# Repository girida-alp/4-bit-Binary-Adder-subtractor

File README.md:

# 4-bit-Binary-Adder-subtractor
4-bit binary calculator grew from my curiosity about digital electronics. Built without a microcontroller, it performs binary addition and subtraction using logic gates, switches, and LEDs, while documenting my journey from Proteus simulation and breadboard testing to KiCad PCB design.
Full Adder — Simulation, Schematic & PCB Design

This repository contains the complete design and implementation of a 1-bit Full Adder, including its logic simulation, KiCad schematics, PCB design, and IC footprints.

📁 Repository Contents

Full Adder Simulation

Logic simulation of the full adder
Verification of Sum and Carry outputs
Truth-table-based testing

KiCad Schematics

Full adder circuit schematics
Logic gate and IC connections
Complete circuit documentation

PCB Design

PCB layout designed in KiCad
Component placement and routing
Board design files ready for manufacturing

IC Footprints

Footprints for each IC used in the circuit
Custom and/or KiCad library footprints
Component placement references for the PCB
🧮 Full Adder

A full adder is a combinational logic circuit that adds three binary inputs:

A — First input
B — Second input
Cin — Carry input

It produces two outputs:

Sum
Cout — Carry output

The circuit can be represented as:

Sum = A ⊕ B ⊕ Cin

Cout = AB + ACin + BCin

🛠️ Tools Used
KiCad — Schematic capture, PCB design, and footprints
Logic Simulation Software — Full adder simulation and verification
🎯 Project Goals

The purpose of this project is to demonstrate the complete hardware-design workflow, from digital logic simulation to schematic design, PCB layout, and physical component footprints.

📂 Project Structure
Full-Adder/
├── Simulation/
│   └── Full-Adder-Simulation
│
├── Schematics/
│   └── Full-Adder.kicad_sch
│
├── PCB/
│   └── Full-Adder.kicad_pcb
│
├── Footprints/
│   └── IC-Footprints/
│
└── README.md

📌 Project Status

Completed — simulation, schematic, PCB design, and IC footprints are included in this repository.

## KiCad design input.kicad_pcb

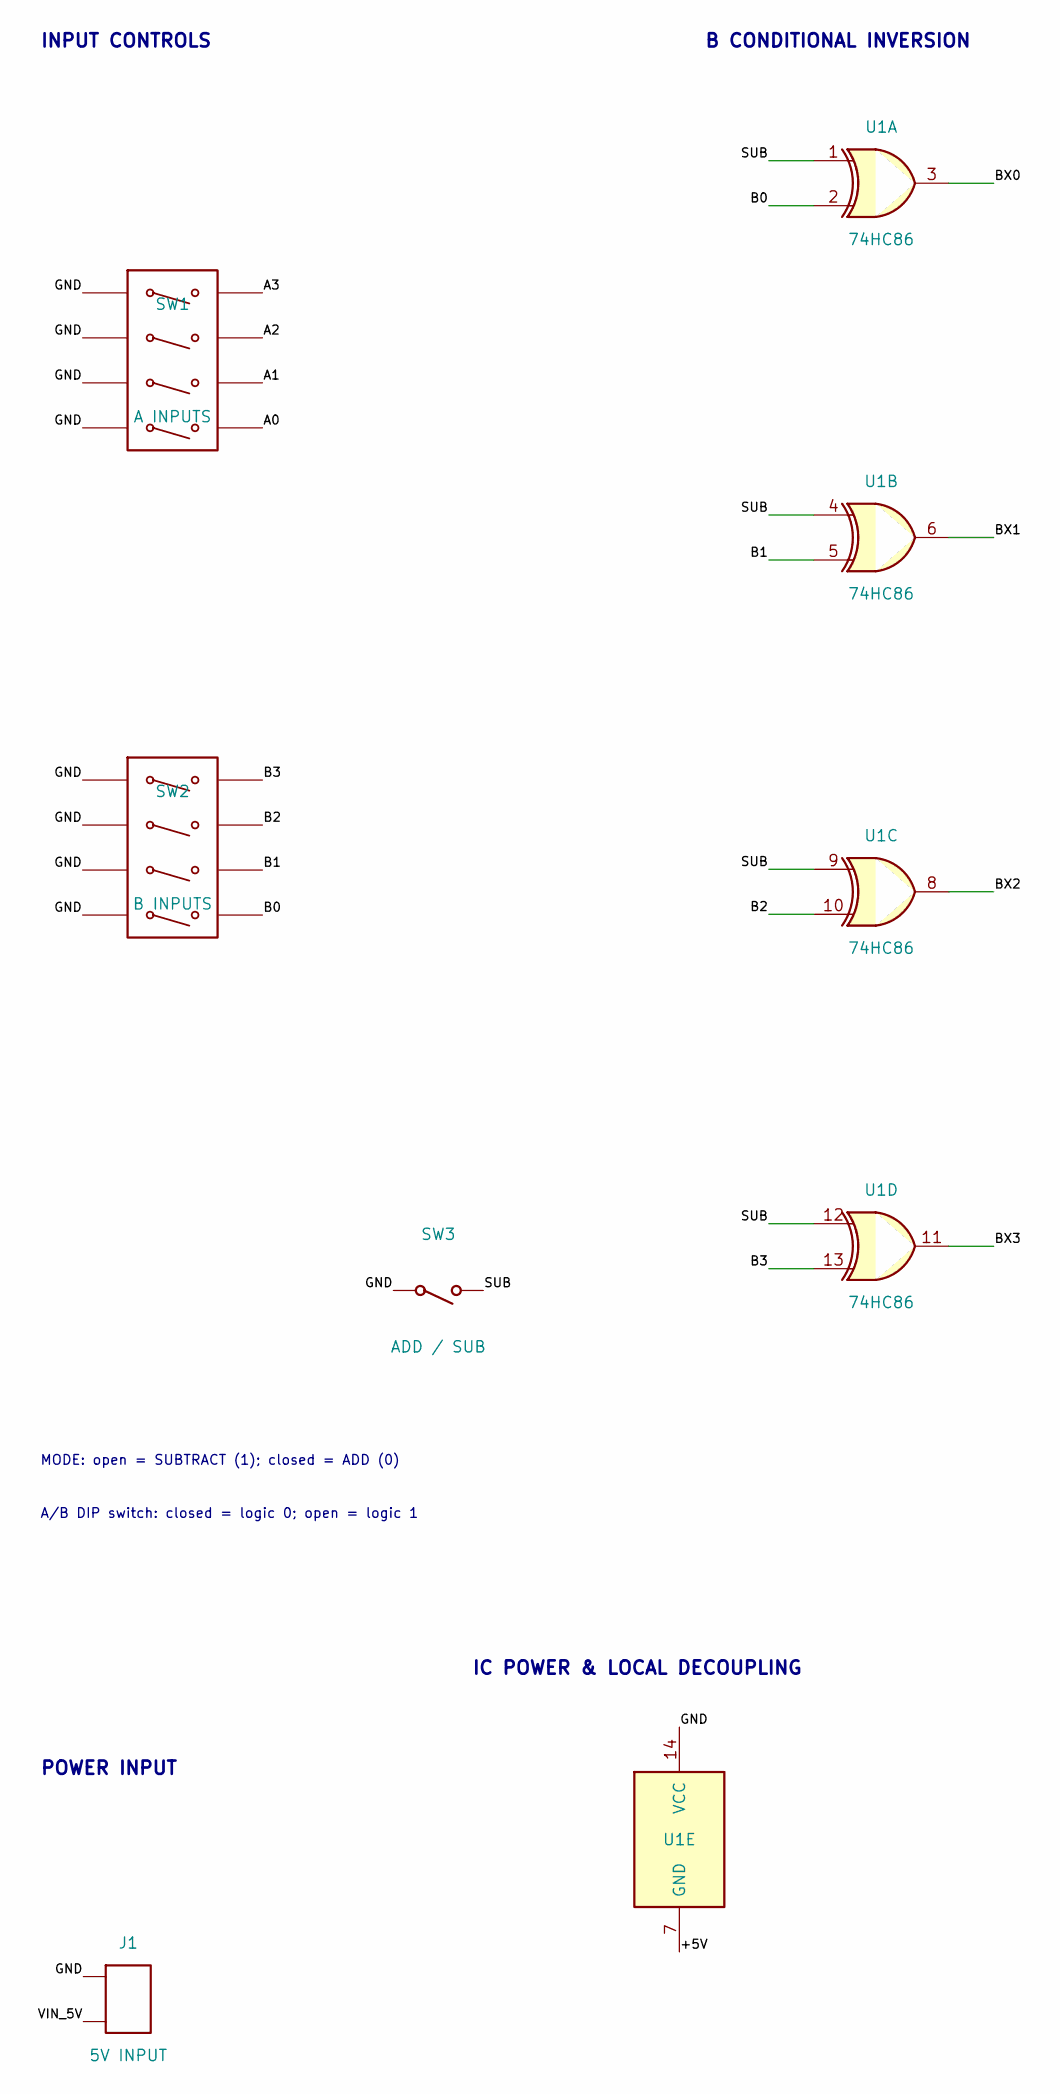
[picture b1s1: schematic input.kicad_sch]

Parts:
J1: 5V INPUT; TerminalBlock_Phoenix_MKDS-1,5-2_1x02_P5.00mm_Horizontal
SW1: A INPUTS; SW_DIP_SPSTx04_Slide_9.78x12.34mm_W7.62mm_P2.54mm
SW2: B INPUTS; SW_DIP_SPSTx04_Slide_9.78x12.34mm_W7.62mm_P2.54mm
SW3: ADD / SUB; SW_DIP_SPSTx01_Slide_9.78x4.72mm_W7.62mm_P2.54mm
U1: 74HC86; DIP-14_W7.62mm

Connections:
/+5V: U1.7 (GND)
/A0: SW1.5 (SW4)
/A1: SW1.6 (SW3)
/A2: SW1.7 (SW2)
/A3: SW1.8 (SW1)
/B0: SW2.5 (SW4), U1.2
/B1: SW2.6 (SW3), U1.5
/B2: SW2.7 (SW2), U1.10
/B3: SW2.8 (SW1), U1.13
/BX0: U1.3
/BX1: U1.6
/BX2: U1.8
/BX3: U1.11
/GND: J1.1, SW1.1 (SW1), SW1.2 (SW2), SW1.3 (SW3), SW1.4 (SW4), SW2.1 (SW1), SW2.2 (SW2), SW2.3 (SW3), SW2.4 (SW4), SW3.1, U1.14 (VCC)
/SUB: SW3.2, U1.1, U1.4, U1.9, U1.12
/VIN_5V: J1.2

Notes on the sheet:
A/B DIP switch: closed = logic 0; open = logic 1
B CONDITIONAL INVERSION
POWER INPUT
MODE: open = SUBTRACT (1); closed = ADD (0)
IC POWER & LOCAL DECOUPLING
INPUT CONTROLS

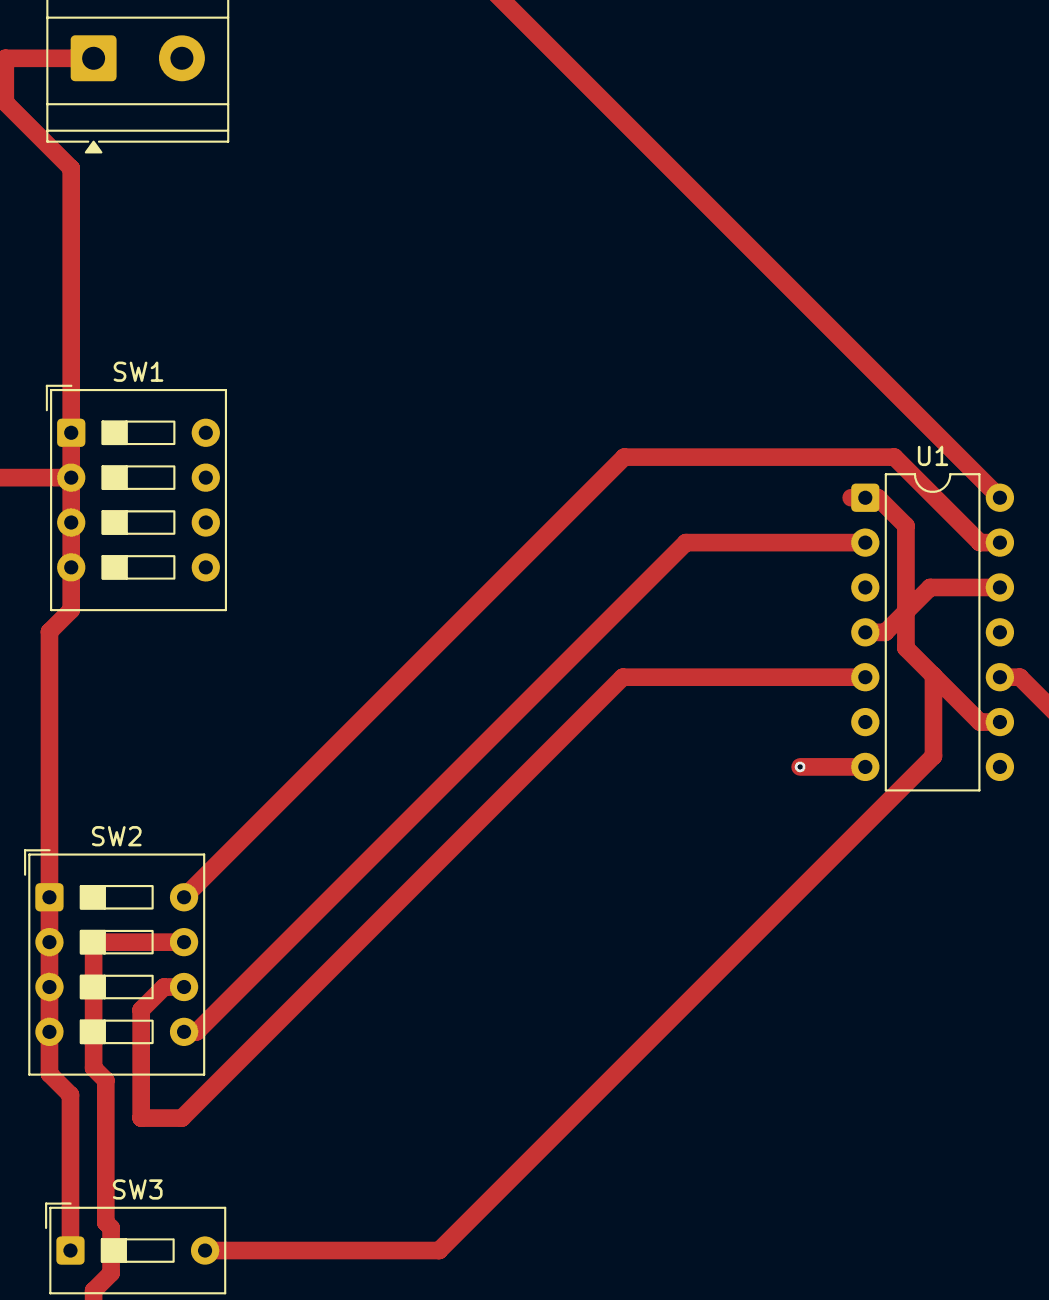
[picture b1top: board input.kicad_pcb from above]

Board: 2 copper layers, 5 parts (0 on the bottom side), 6 nets.

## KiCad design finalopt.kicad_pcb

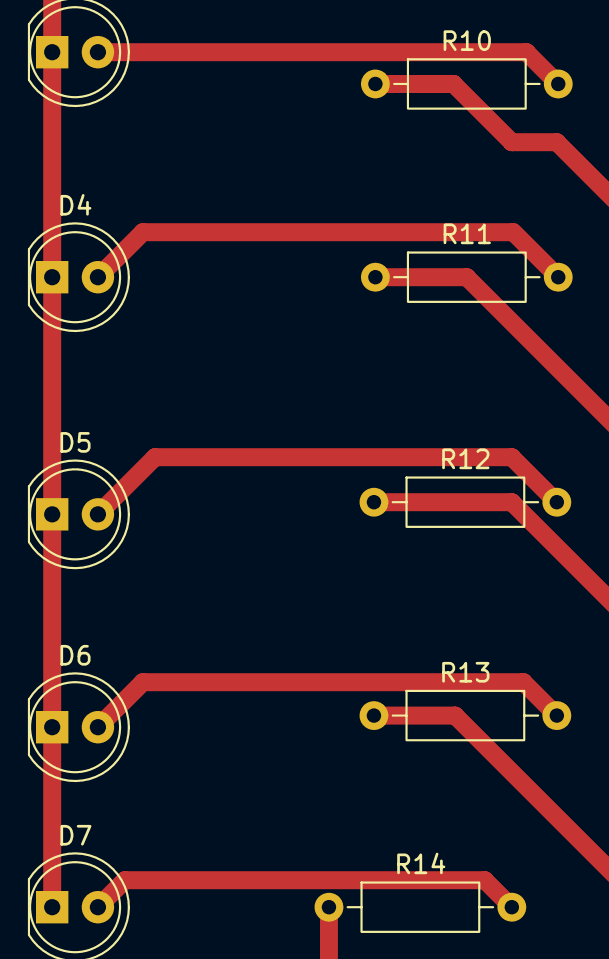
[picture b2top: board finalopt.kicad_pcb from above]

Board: 2 copper layers, 10 parts (0 on the bottom side), 6 nets.

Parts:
D3: S0; LED_D5.0mm
D4: S1; LED_D5.0mm
D5: S2; LED_D5.0mm
D6: S3; LED_D5.0mm
D7: C4; LED_D5.0mm
R10, R11, R12, R13, R14: 4.7k; R_Axial_DIN0207_L6.3mm_D2.5mm_P10.16mm_Horizontal

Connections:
/GND: D3.1 (K), D4.1 (K), D5.1 (K), D6.1 (K), D7.1 (K)
unnamed: D3.2 (A), R10.2
unnamed: D4.2 (A), R11.2
unnamed: D5.2 (A), R12.2
unnamed: D6.2 (A), R13.2
unnamed: D7.2 (A), R14.2

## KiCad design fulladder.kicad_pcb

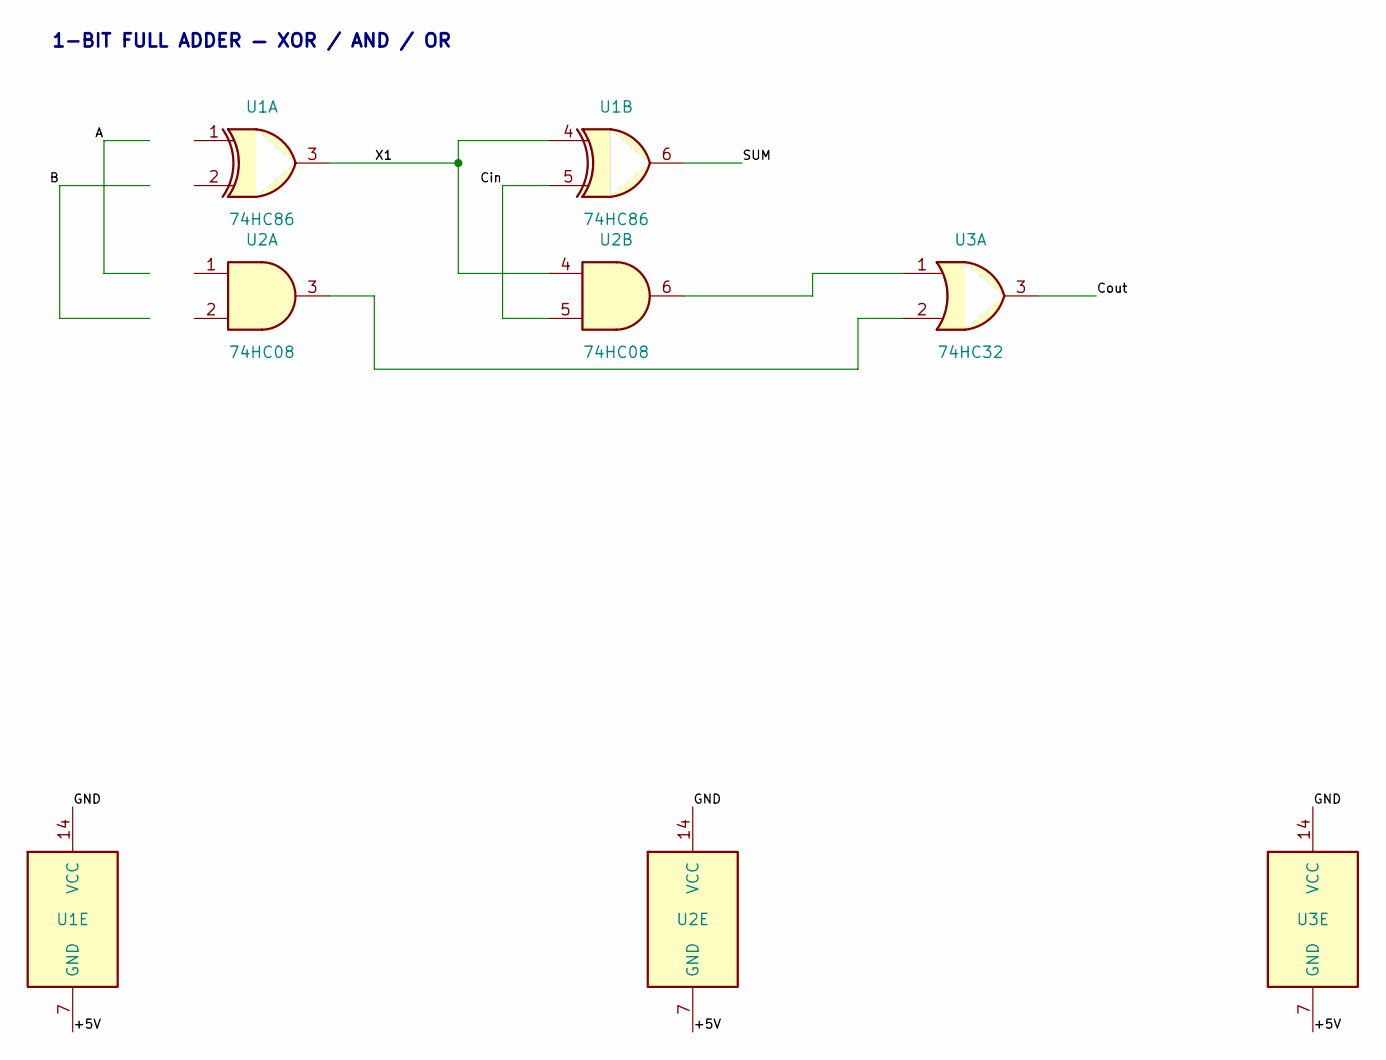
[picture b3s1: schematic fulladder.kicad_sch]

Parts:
U1: 74HC86; DIP-14_W7.62mm
U2: 74HC08; DIP-14_W7.62mm
U3: 74HC32; DIP-14_W7.62mm

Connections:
/+5V: U1.7 (GND), U2.7 (GND), U3.7 (GND)
/Cin: U1.5, U2.5
/Cout: U3.3
/GND: U1.14 (VCC), U2.14 (VCC), U3.14 (VCC)
/SUM: U1.6
/X1: U1.3, U1.4, U2.4
unnamed: U2.3, U3.2
unnamed: U2.6, U3.1

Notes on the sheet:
1-BIT FULL ADDER — XOR / AND / OR

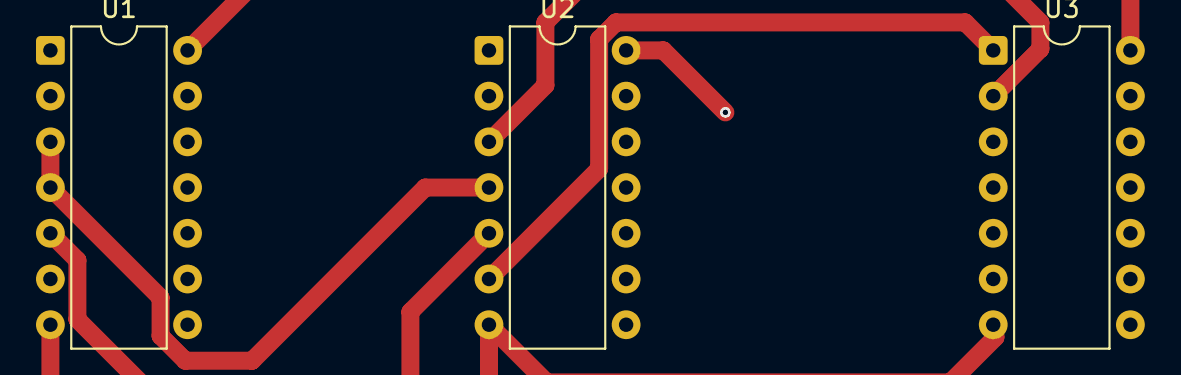
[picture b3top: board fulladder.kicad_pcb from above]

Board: 2 copper layers, 3 parts (0 on the bottom side), 6 nets.
